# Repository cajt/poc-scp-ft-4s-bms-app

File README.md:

# poc-scp-ft-4s-bms-app
Proof of concept fault tolerant SCP with a BMS Application.

# Fault Tolerance Concept

Fail-safe in a 2-out-of-2 configuration. BMS is implemented in split parts. Both halves have to error 
free for the battery/BMS to operate nominally. 
If an error is detected the whole system stops and the electronics disconnects the battery cells from 
the rest of the system, protecting the cells from leaving their safe operating area in the presence 
of BMS error.

In the error-free operation simple cell safety limits are checked: Cell voltages, Current and Temperatures.

# Simplifications for the PoC

- Power supply: Non-redundant and externally supplied.
- Wake-up and power boot-strap: None, the system can't wake up without an external power source. 
- Only 4 cells. (But it should moderately obvious how to extend this by a few more cells. Conceptually this is also compatible with stacking the BMS for higher cells counts.)

# Motivation

Li based cells have some nasty failure-modes, and require some attention to avoid entering dangerous operating areas. This is a good application for fault-tolerance and fail-safe circuitry

# Disclaimer, Liabilities and Guarantees

No Guarantees. The risk is yours alone. If you don't understand this method, mitigation and risks involved you should really not touch this. 
Published in the hope that it might be inspiration or food for thought, not a ready to use module or product.

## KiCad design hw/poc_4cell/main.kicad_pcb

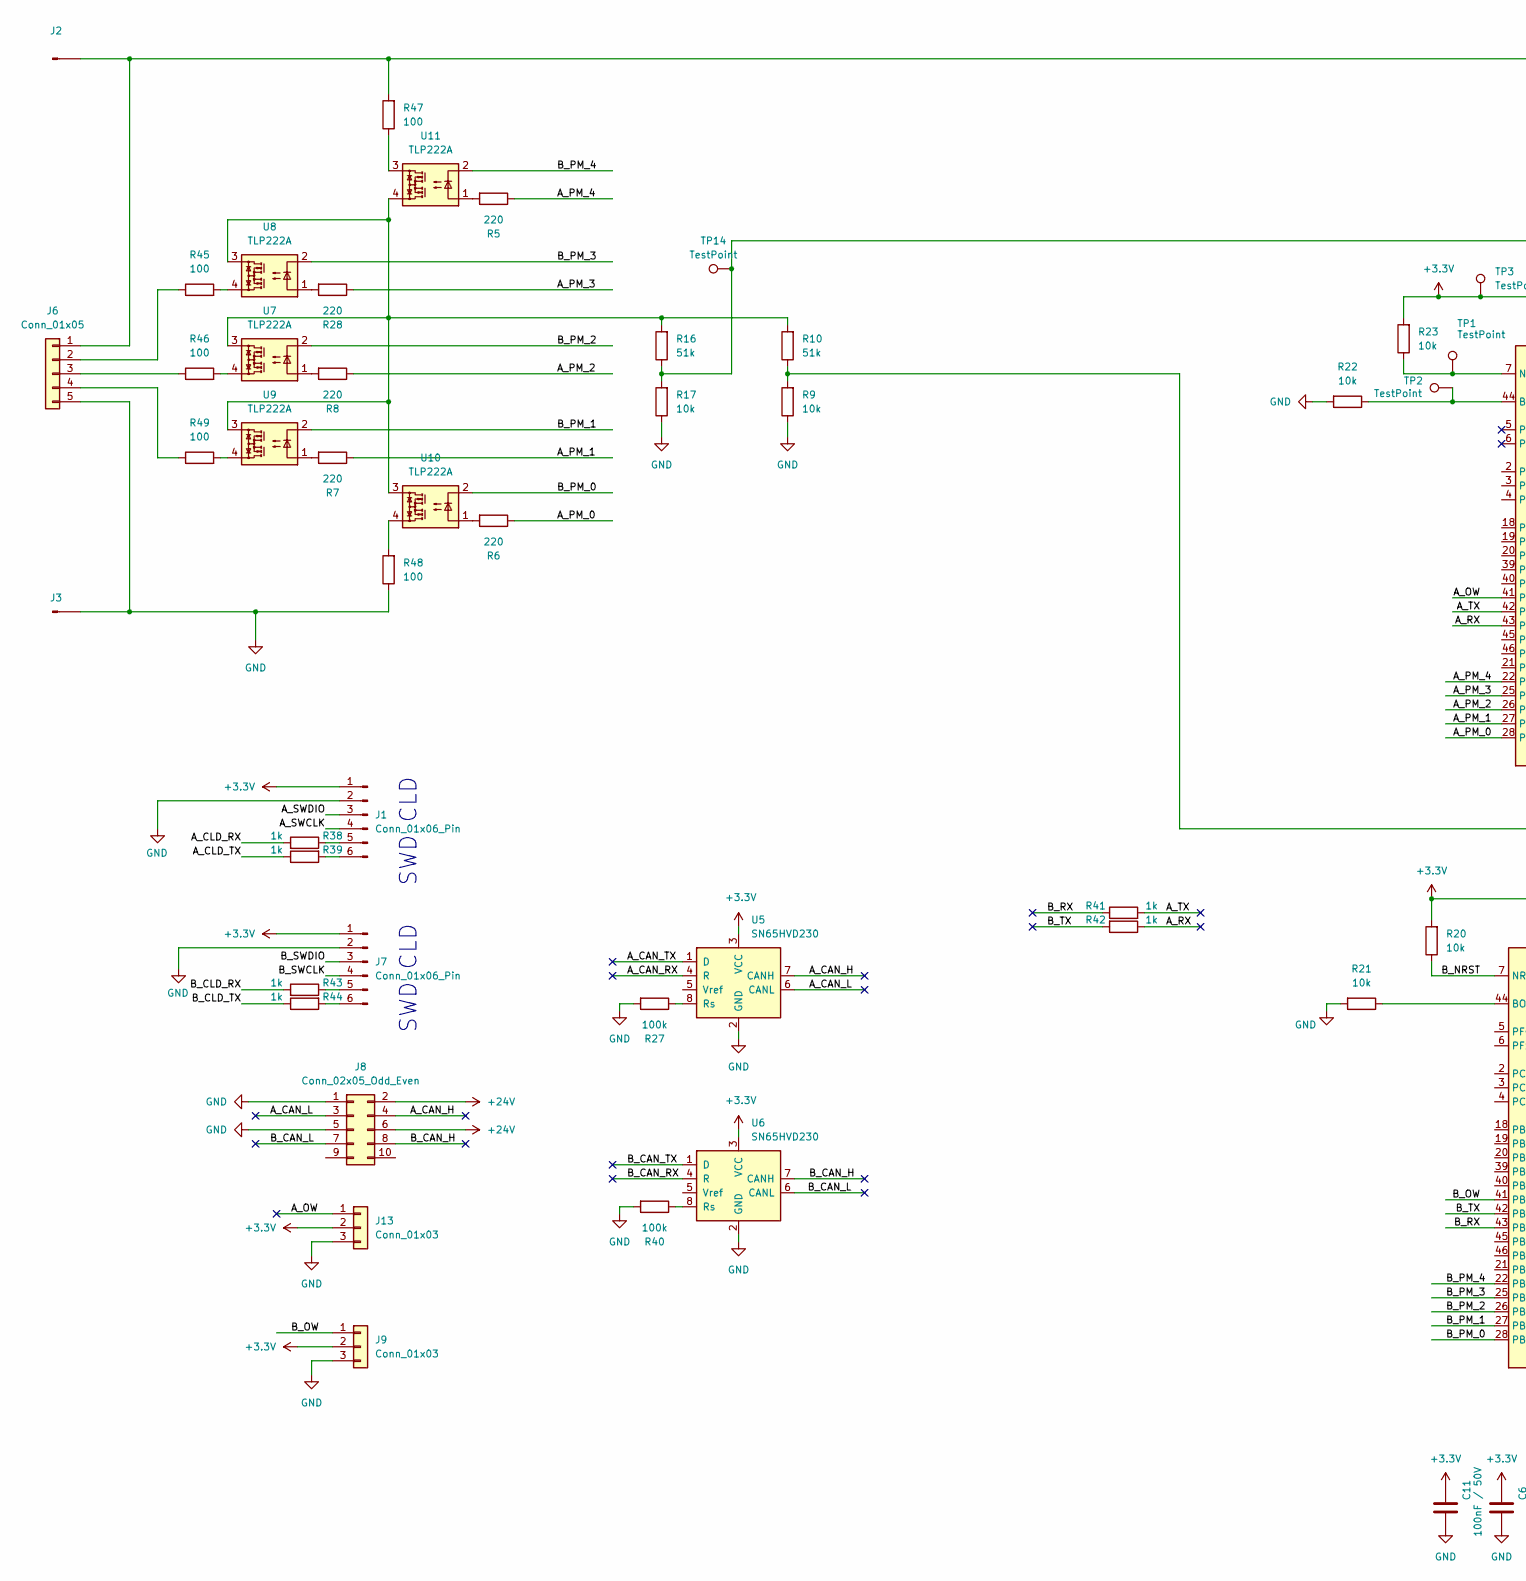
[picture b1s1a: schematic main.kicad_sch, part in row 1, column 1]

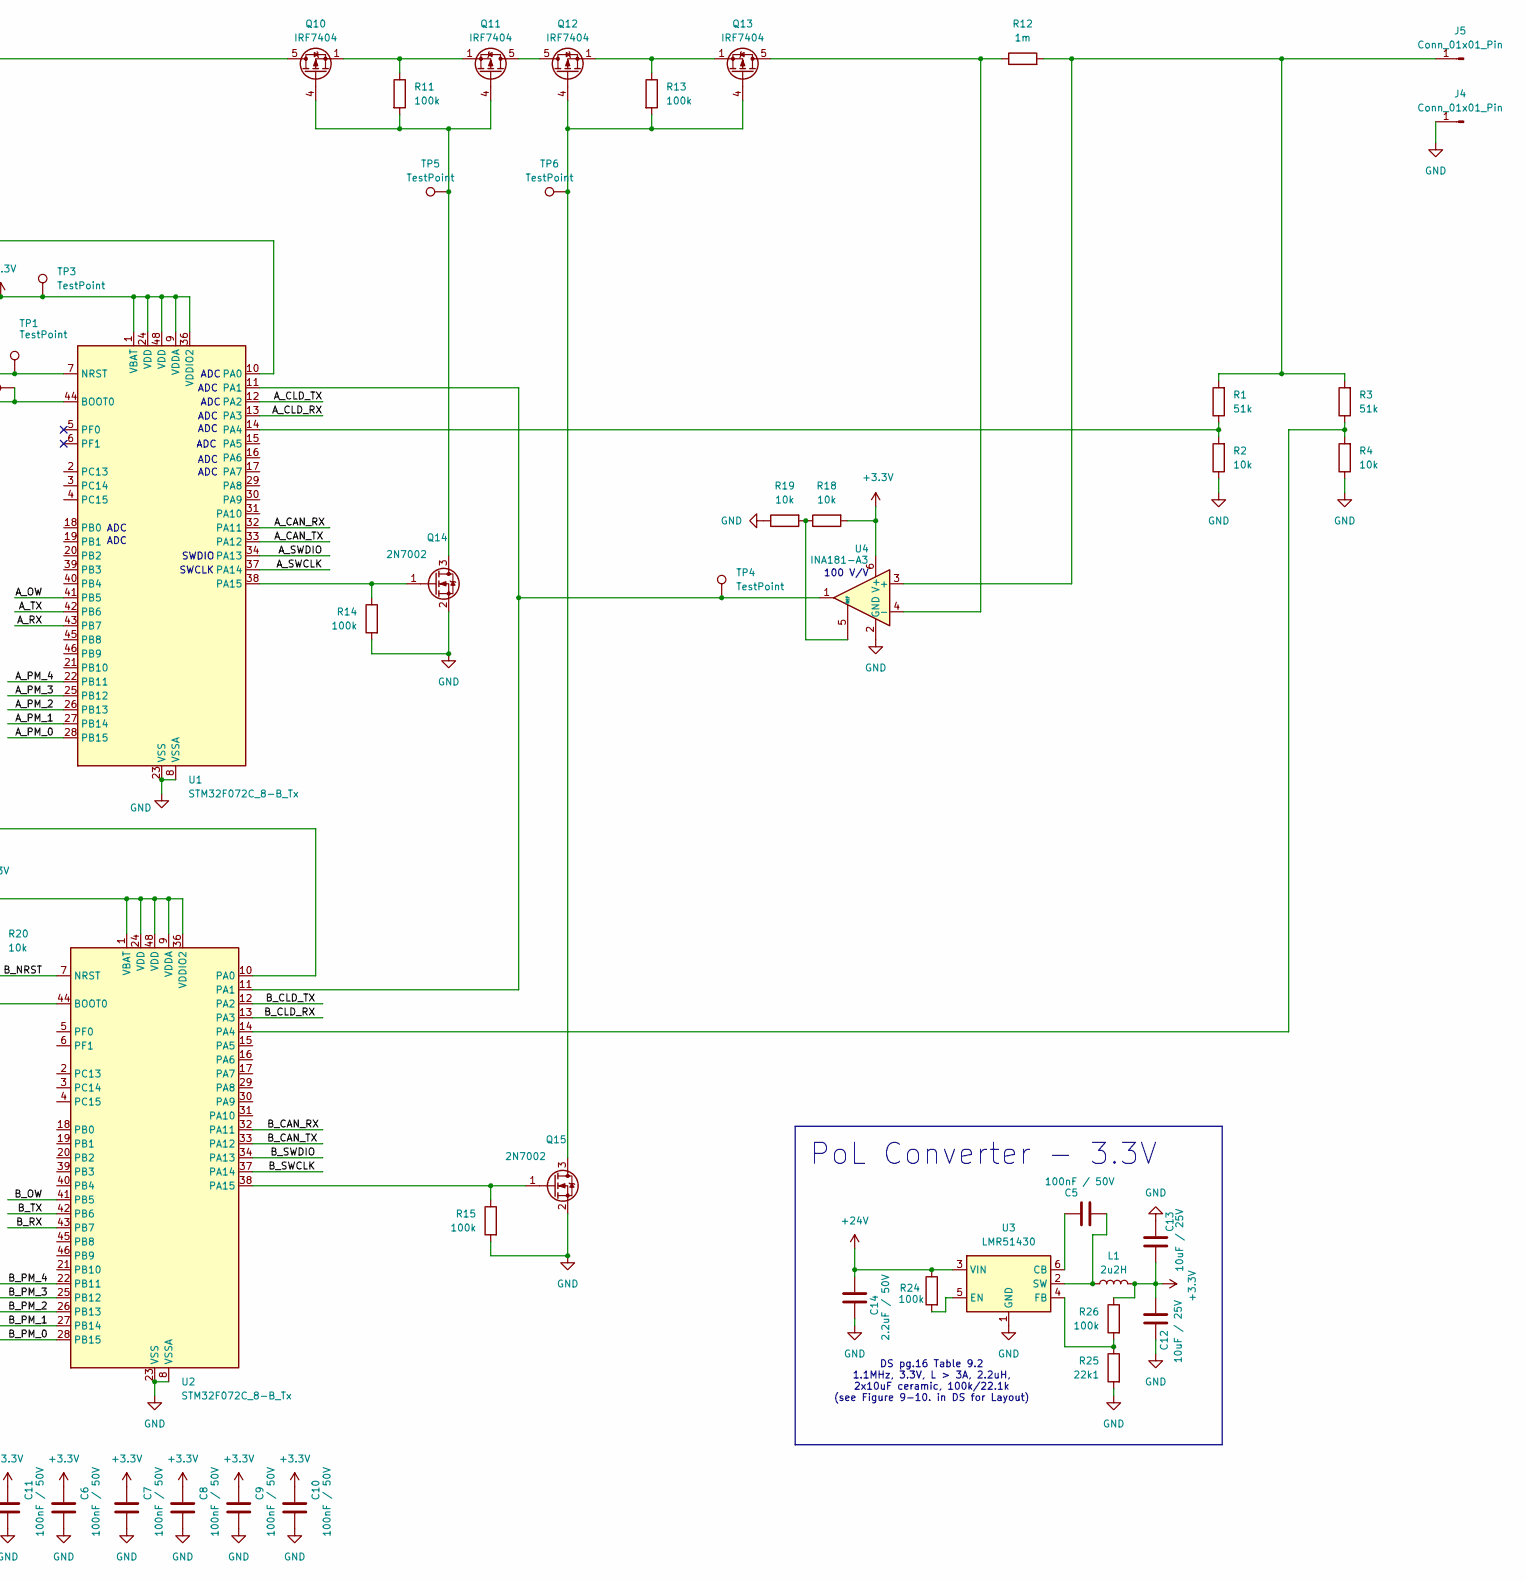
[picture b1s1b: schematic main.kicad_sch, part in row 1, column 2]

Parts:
C5, C6, C7, C8, C9, C10, C11: 100nF / 50V; C_0603_1608Metric
C12, C13: 10uF / 25V; C_0603_1608Metric
C14: 2.2uF / 50V; C_0603_1608Metric
J1, J7: Conn_01x06_Pin; JST_GH_SM05B-GHS-TB_1x05-1MP_P1.25mm_Horizontal
J2, J3, J4, J5: Conn_01x01_Pin; MountingHole_3.2mm_M3_DIN965_Pad
J6: Conn_01x05; JST_XH_B5B-XH-AM_1x05_P2.50mm_Vertical
J8: Conn_02x05_Odd_Even; PinHeader_2x05_P2.54mm_Horizontal
J9, J13: Conn_01x03; JST_GH_SM03B-GHS-TB_1x03-1MP_P1.25mm_Horizontal
L1: 2u2H; L_1210_3225Metric_Pad1.42x2.65mm_HandSolder; mfg# DFE322520F-2R2M=P2
Q10, Q11, Q12, Q13: IRF7404; SOIC-8_3.9x4.9mm_P1.27mm
Q14, Q15: 2N7002; SOT-23
R1, R3, R10, R16: 51k; R_0603_1608Metric
R2, R4, R9, R17, R18, R19, R20, R21, R22, R23: 10k; R_0603_1608Metric
R5, R6, R7, R8, R28: 220; R_0603_1608Metric
R11, R13, R14, R15, R24, R26, R27, R40: 100k; R_0603_1608Metric
R12: 1m; R_2512_6332Metric
R25: 22k1; R_0603_1608Metric
R38, R39, R41, R42, R43, R44: 1k; R_0805_2012Metric
R45, R46, R47, R48, R49: 100; R_1206_3216Metric
TP1, TP2, TP3, TP4, TP5, TP6, TP14: TestPoint; TestPoint_Pad_D1.5mm
U1, U2: STM32F072C_8-B_Tx; LQFP-48_7x7mm_P0.5mm
U3: LMR51430; SOT-23-6
U4: INA181-A3; SOT-23-6
U5, U6: SN65HVD230; SOIC-8_3.9x4.9mm_P1.27mm
U7, U8, U9, U10, U11: TLP222A; DIP-4_W7.62mm

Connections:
+3.3V: C6.1, C7.1, C8.1, C9.1, C10.1, C11.1, C12.1, C13.1, J1.1, J7.1, J9.2, J13.2, L1.2, R18.2, R20.2, R23.2, R26.1, TP3.1, U1.1 (VBAT), U1.9 (VDDA), U1.24 (VDD), U1.36 (VDDIO2), U1.48 (VDD), U2.1 (VBAT), U2.9 (VDDA), U2.24 (VDD), U2.36 (VDDIO2), U2.48 (VDD), U4.6 (V+), U5.3 (VCC), U6.3 (VCC)
+24V: C14.1, J8.2, J8.6, R24.1, U3.3 (VIN)
/A_CAN_H: J8.4, U5.7 (CANH)
/A_CAN_L: J8.3, U5.6 (CANL)
/A_CAN_RX: U1.32 (PA11), U5.4 (R)
/A_CAN_TX: U1.33 (PA12), U5.1 (D)
/A_CLD_RX: R38.2, U1.13 (PA3)
/A_CLD_TX: R39.1, U1.12 (PA2)
/A_OW: J13.1, U1.41 (PB5)
/A_PM_0: R6.1, U1.28 (PB15)
/A_PM_1: R7.1, U1.27 (PB14)
/A_PM_2: R8.1, U1.26 (PB13)
/A_PM_3: R28.1, U1.25 (PB12)
/A_PM_4: R5.1, U1.22 (PB11)
/A_RX: R42.1, U1.43 (PB7)
/A_SWCLK: J1.4, U1.37 (PA14)
/A_SWDIO: J1.3, U1.34 (PA13)
/A_TX: R41.2, U1.42 (PB6)
/B_CAN_H: J8.8, U6.7 (CANH)
/B_CAN_L: J8.7, U6.6 (CANL)
/B_CAN_RX: U2.32 (PA11), U6.4 (R)
/B_CAN_TX: U2.33 (PA12), U6.1 (D)
/B_CLD_RX: R43.2, U2.13 (PA3)
/B_CLD_TX: R44.1, U2.12 (PA2)
/B_NRST: R20.1, U2.7 (NRST)
/B_OW: J9.1, U2.41 (PB5)
/B_PM_0: U2.28 (PB15), U10.2
/B_PM_1: U2.27 (PB14), U9.2
/B_PM_2: U2.26 (PB13), U7.2
/B_PM_3: U2.25 (PB12), U8.2
/B_PM_4: U2.22 (PB11), U11.2
/B_RX: R41.1, U2.43 (PB7)
/B_SWCLK: J7.4, U2.37 (PA14)
/B_SWDIO: J7.3, U2.34 (PA13)
/B_TX: R42.2, U2.42 (PB6)
GND: C6.2, C7.2, C8.2, C9.2, C10.2, C11.2, C12.2, C13.2, C14.2, J1.2, J3.1, J4.1, J6.5, J7.2, J8.1, J8.5, J9.3, J13.3, Q14.2 (S), Q15.2 (S), R2.1, R4.1, R9.1, R14.2, R15.2, R17.1, R19.1, R21.2, R22.2, R25.2, R27.2, R40.2, R48.1, U1.8 (VSSA), U1.23 (VSS), U1.35 (VSS), U1.47 (VSS), U2.8 (VSSA), U2.23 (VSS), U2.35 (VSS), U2.47 (VSS), U3.1 (GND), U4.2 (GND), U5.2 (GND), U6.2 (GND)
unnamed: J1.5, R38.1
unnamed: J1.6, R39.2
unnamed: J2.1, J6.1, Q10.5 (D), Q10.6 (D), Q10.7 (D), Q10.8 (D), R47.2
unnamed: J5.1, R1.2, R3.2, R12.2, U4.3 (+)
unnamed: J6.2, R45.1
unnamed: J6.3, R46.1
unnamed: J6.4, R49.1
unnamed: J7.5, R43.1
unnamed: J7.6, R44.2
unnamed: Q10.4 (G), Q11.4 (G), Q14.3 (D), R11.2, TP5.1
unnamed: Q10.1 (S), Q10.2 (S), Q10.3 (S), Q11.1 (S), Q11.2 (S), Q11.3 (S), R11.1
unnamed: Q11.5 (D), Q11.6 (D), Q11.7 (D), Q11.8 (D), Q12.5 (D), Q12.6 (D), Q12.7 (D), Q12.8 (D)
unnamed: Q12.4 (G), Q13.4 (G), Q15.3 (D), R13.2, TP6.1
unnamed: Q12.1 (S), Q12.2 (S), Q12.3 (S), Q13.1 (S), Q13.2 (S), Q13.3 (S), R13.1
unnamed: Q14.1 (G), R14.1, U1.38 (PA15)
unnamed: Q15.1 (G), R15.1, U2.38 (PA15)
unnamed: R5.2, U11.1
unnamed: R6.2, U10.1
unnamed: R7.2, U9.1
unnamed: R8.2, U7.1
unnamed: R10.2, R16.2, U7.3, U8.3, U9.3, U10.3, U11.4
unnamed: R28.2, U8.1
unnamed: R45.2, U8.4
unnamed: R46.2, U7.4
unnamed: R47.1, U11.3
unnamed: R48.2, U10.4
unnamed: R49.2, U9.4
unnamed: R22.1, TP2.1, U1.44 (BOOT0)
unnamed: R23.1, TP1.1, U1.7 (NRST)
unnamed: R16.1, R17.2, TP14.1, U1.10 (PA0)
unnamed: TP4.1, U1.11 (PA1), U2.11 (PA1), U4.1
unnamed: R1.1, R2.2, U1.14 (PA4)
unnamed: R21.1, U2.44 (BOOT0)
unnamed: R9.2, R10.1, U2.10 (PA0)
unnamed: R3.1, R4.2, U2.14 (PA4)
unnamed: C5.1, U3.6 (CB)
unnamed: R24.2, U3.5 (EN)
unnamed: R25.1, R26.2, U3.4 (FB)
unnamed: C5.2, L1.1, U3.2 (SW)
unnamed: Q13.5 (D), Q13.6 (D), Q13.7 (D), Q13.8 (D), R12.1, U4.4 (-)
unnamed: R18.1, R19.2, U4.5 (REF)
unnamed: R27.1, U5.8 (Rs)
unnamed: R40.1, U6.8 (Rs)

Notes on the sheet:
SWCLK
ADC
CLD
SWD
DS pg.16 Table 9.2 1.1MHz, 3.3V, L > 3A, 2.2uH, 2x10uF ceramic, 100k/22.1k (see Figure 9-10. in DS for Layout)
PoL Converter - 3.3V
100 V/V
SWDIO

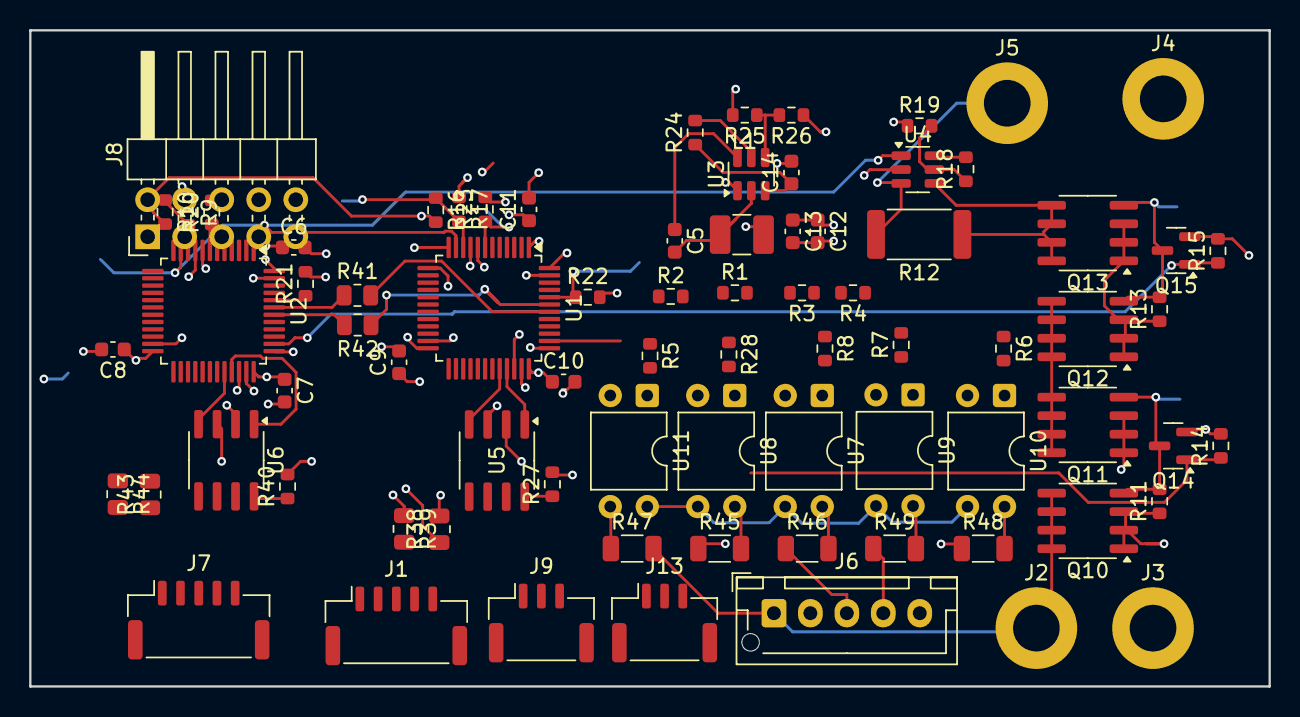
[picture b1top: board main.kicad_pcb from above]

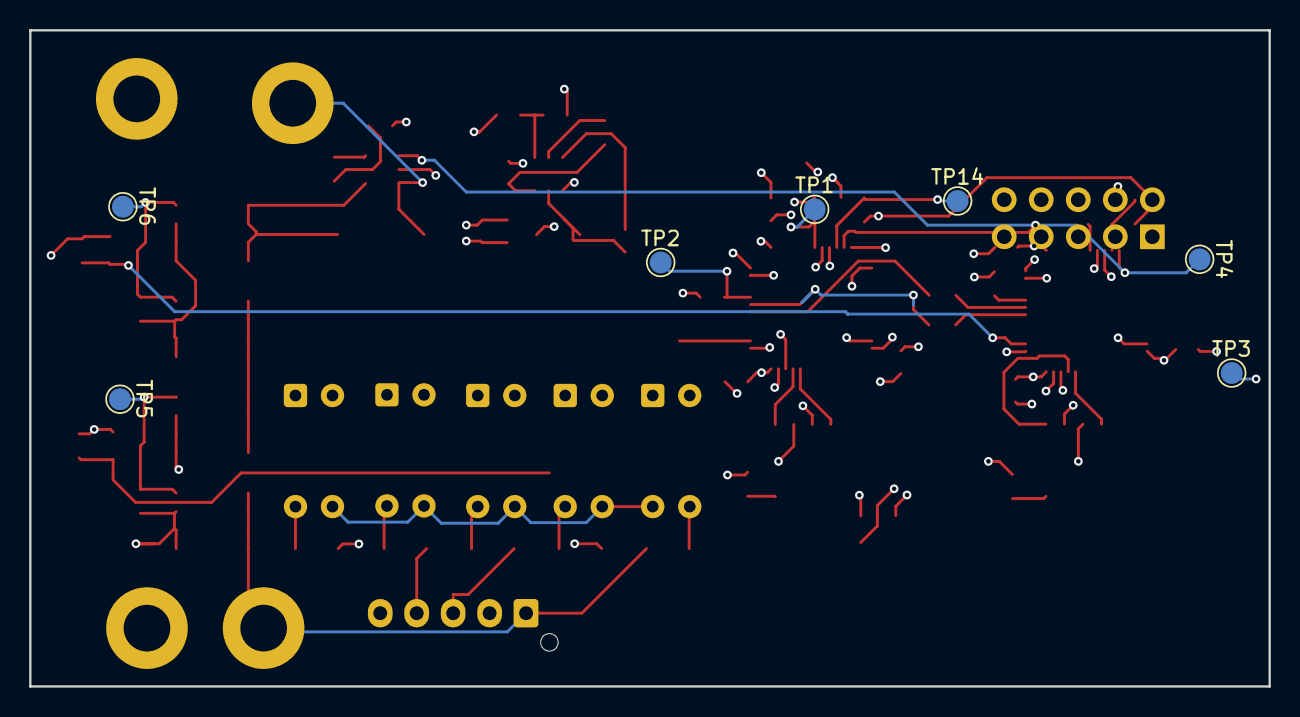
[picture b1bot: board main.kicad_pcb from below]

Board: 4 copper layers, 85.0 x 45.0 mm, 85 parts (7 on the bottom side), 77 nets.

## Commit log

2025-12-23 Enhance README with fault tolerance details
    Added detailed explanations about fault tolerance, simplifications for the proof of concept, and motivation for the design in the README.
2026-01-04 Import a simplified (and unfished) version with electronics for 4 cells.
2026-01-04 Now with a makefile to generate PDF of scheamtics & layout.
